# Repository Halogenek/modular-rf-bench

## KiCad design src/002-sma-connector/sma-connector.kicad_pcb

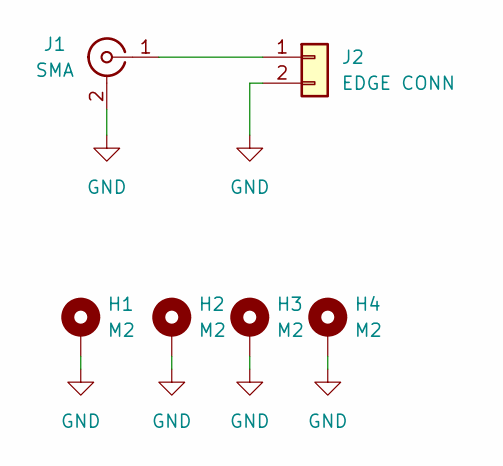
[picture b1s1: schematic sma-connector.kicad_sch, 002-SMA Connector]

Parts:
H1, H2, H3, H4: M2; M2-hole
J1: SMA; SMA_Amphenol_132134-10_Vertical
J2: EDGE CONN; edge-connector

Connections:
GND: H1.1, H2.1, H3.1, H4.1, J1.2 (Ext), J2.2
unnamed: J1.1 (In), J2.1

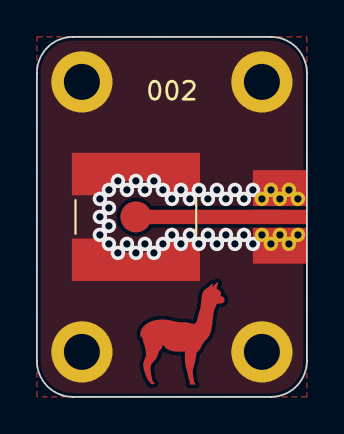
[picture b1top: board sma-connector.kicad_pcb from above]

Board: 2 copper layers, 15.0 x 20.0 mm, 6 parts (0 on the bottom side), 2 nets.

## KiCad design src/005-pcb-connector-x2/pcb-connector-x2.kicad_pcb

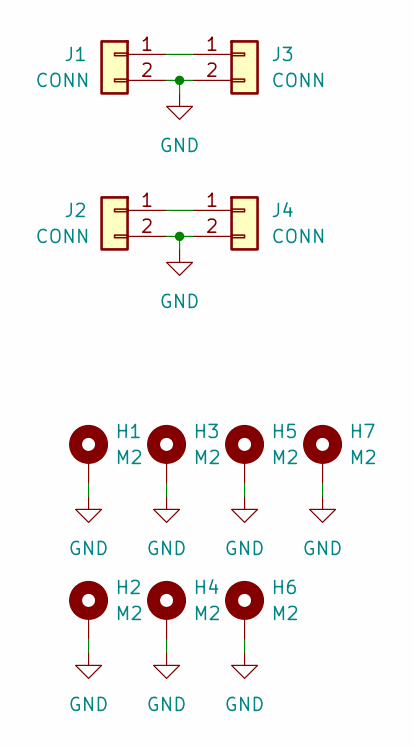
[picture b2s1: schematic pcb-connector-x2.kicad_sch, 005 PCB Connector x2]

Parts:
H1, H2, H3, H4, H5, H6, H7: M2; M2-hole
J1, J2, J3, J4: CONN; edge-connector

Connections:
GND: H1.1, H2.1, H3.1, H4.1, H5.1, H6.1, H7.1, J1.2, J2.2, J3.2, J4.2
unnamed: J1.1, J3.1
unnamed: J2.1, J4.1

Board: 2 copper layers, 11 parts (0 on the bottom side), 3 nets, no tracks yet.

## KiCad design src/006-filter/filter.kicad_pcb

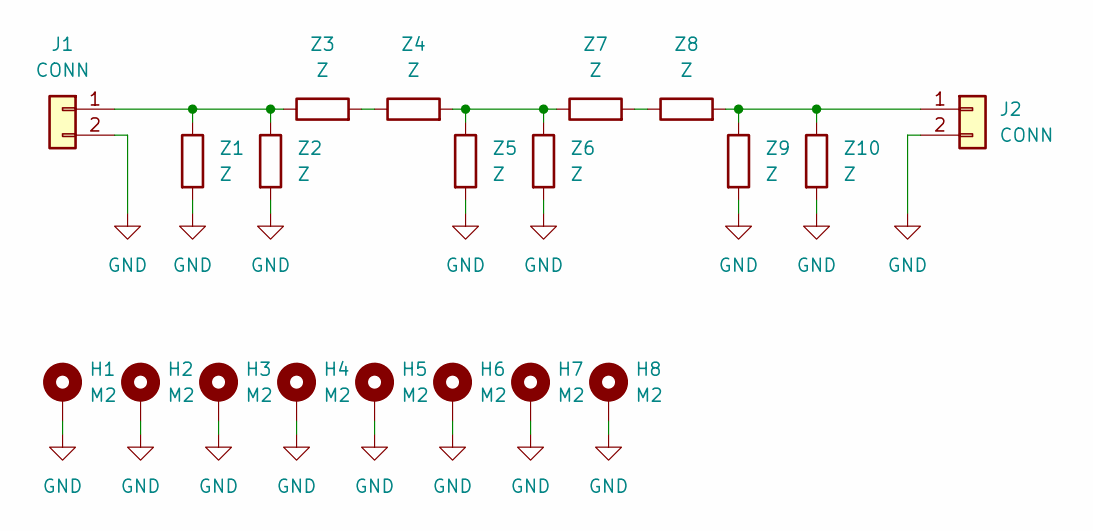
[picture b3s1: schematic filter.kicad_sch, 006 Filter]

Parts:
H1, H2, H3, H4, H5, H6, H7, H8: M2; M2-hole
J1, J2: CONN; edge-connector
Z1, Z2, Z3, Z4, Z5, Z6, Z7, Z8, Z9, Z10: Z; R_0805_2012Metric

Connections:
GND: H1.1, H2.1, H3.1, H4.1, H5.1, H6.1, H7.1, H8.1, J1.2, J2.2, Z1.2, Z2.2, Z5.2, Z6.2, Z9.2, Z10.2
unnamed: J1.1, Z1.1, Z2.1, Z3.1
unnamed: J2.1, Z8.2, Z9.1, Z10.1
unnamed: Z3.2, Z4.1
unnamed: Z4.2, Z5.1, Z6.1, Z7.1
unnamed: Z7.2, Z8.1

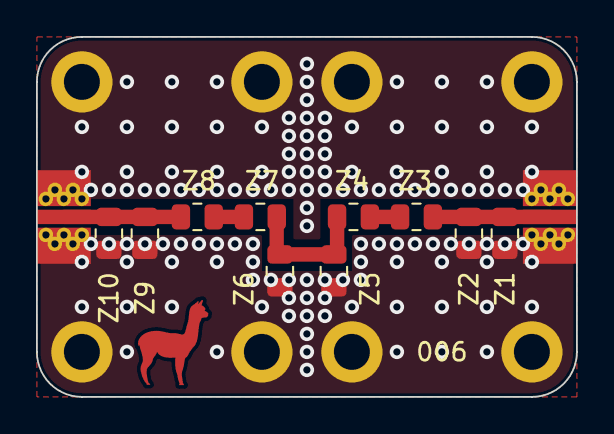
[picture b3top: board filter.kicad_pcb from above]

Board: 2 copper layers, 30.0 x 20.0 mm, 20 parts (0 on the bottom side), 6 nets.

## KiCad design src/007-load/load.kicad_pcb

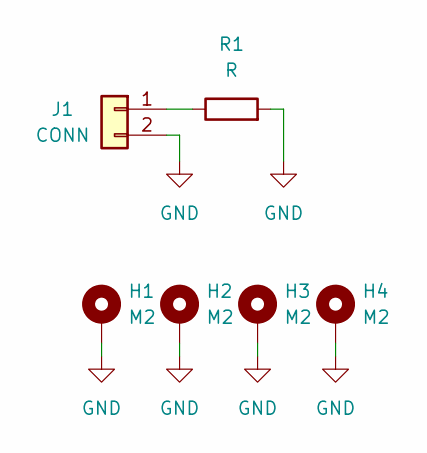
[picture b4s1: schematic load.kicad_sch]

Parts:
H1, H2, H3, H4: M2; M2-hole
J1: CONN; edge-connector
R1: R; R_0805_2012Metric

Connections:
GND: H1.1, H2.1, H3.1, H4.1, J1.2, R1.2
unnamed: J1.1, R1.1

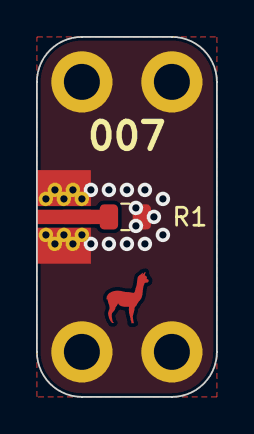
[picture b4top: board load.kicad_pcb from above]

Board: 2 copper layers, 10.0 x 20.0 mm, 6 parts (0 on the bottom side), 2 nets.
